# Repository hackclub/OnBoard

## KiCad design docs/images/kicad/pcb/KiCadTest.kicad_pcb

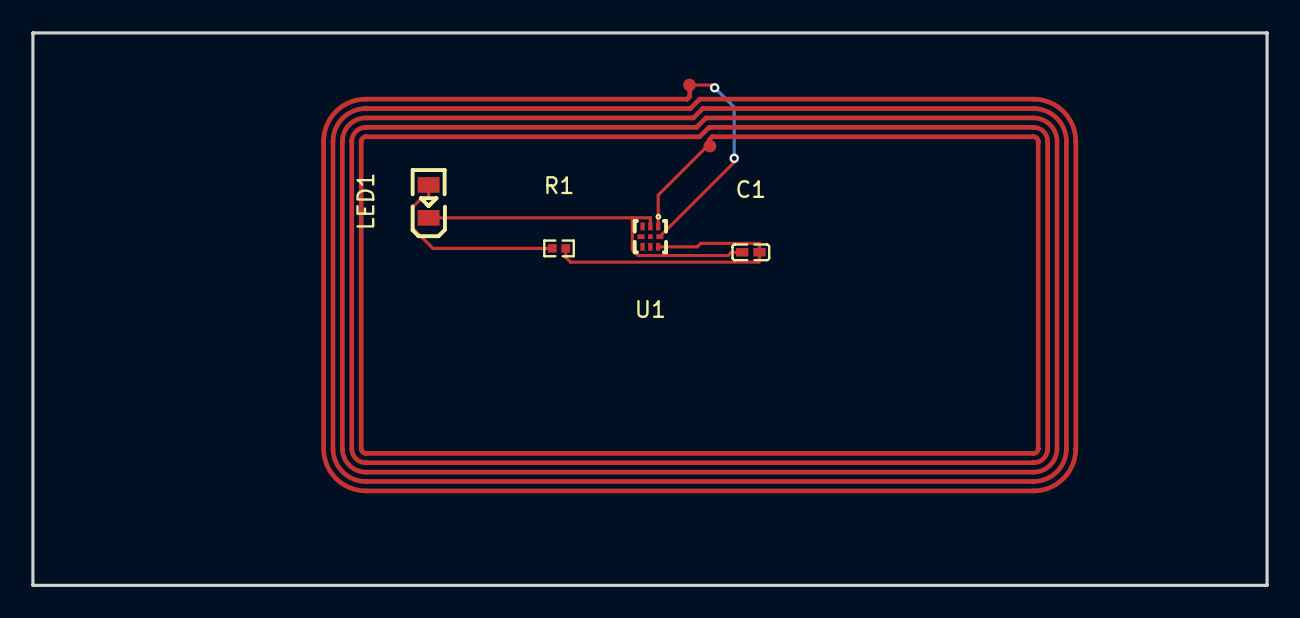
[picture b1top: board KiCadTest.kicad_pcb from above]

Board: 2 copper layers, 78.8 x 35.2 mm, 5 parts (0 on the bottom side), 3 nets.

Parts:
AE1: Antenna_Loop; 25X48MM_NFC_ANTENNA
C1: 220nF; C0402
LED1: 17-21SUYC/TR8; LED0805-R-RD
R1: 47; R0402
U1: NT3H2111W0FHKH; XQFN-8_L1.6-W1.6-P0.50-BL

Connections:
unnamed: LED1.1 (+), R1.1
unnamed: C1.1, LED1.2 (-), U1.2 (VSS)
unnamed: C1.2, R1.2, U1.7 (VOUT)

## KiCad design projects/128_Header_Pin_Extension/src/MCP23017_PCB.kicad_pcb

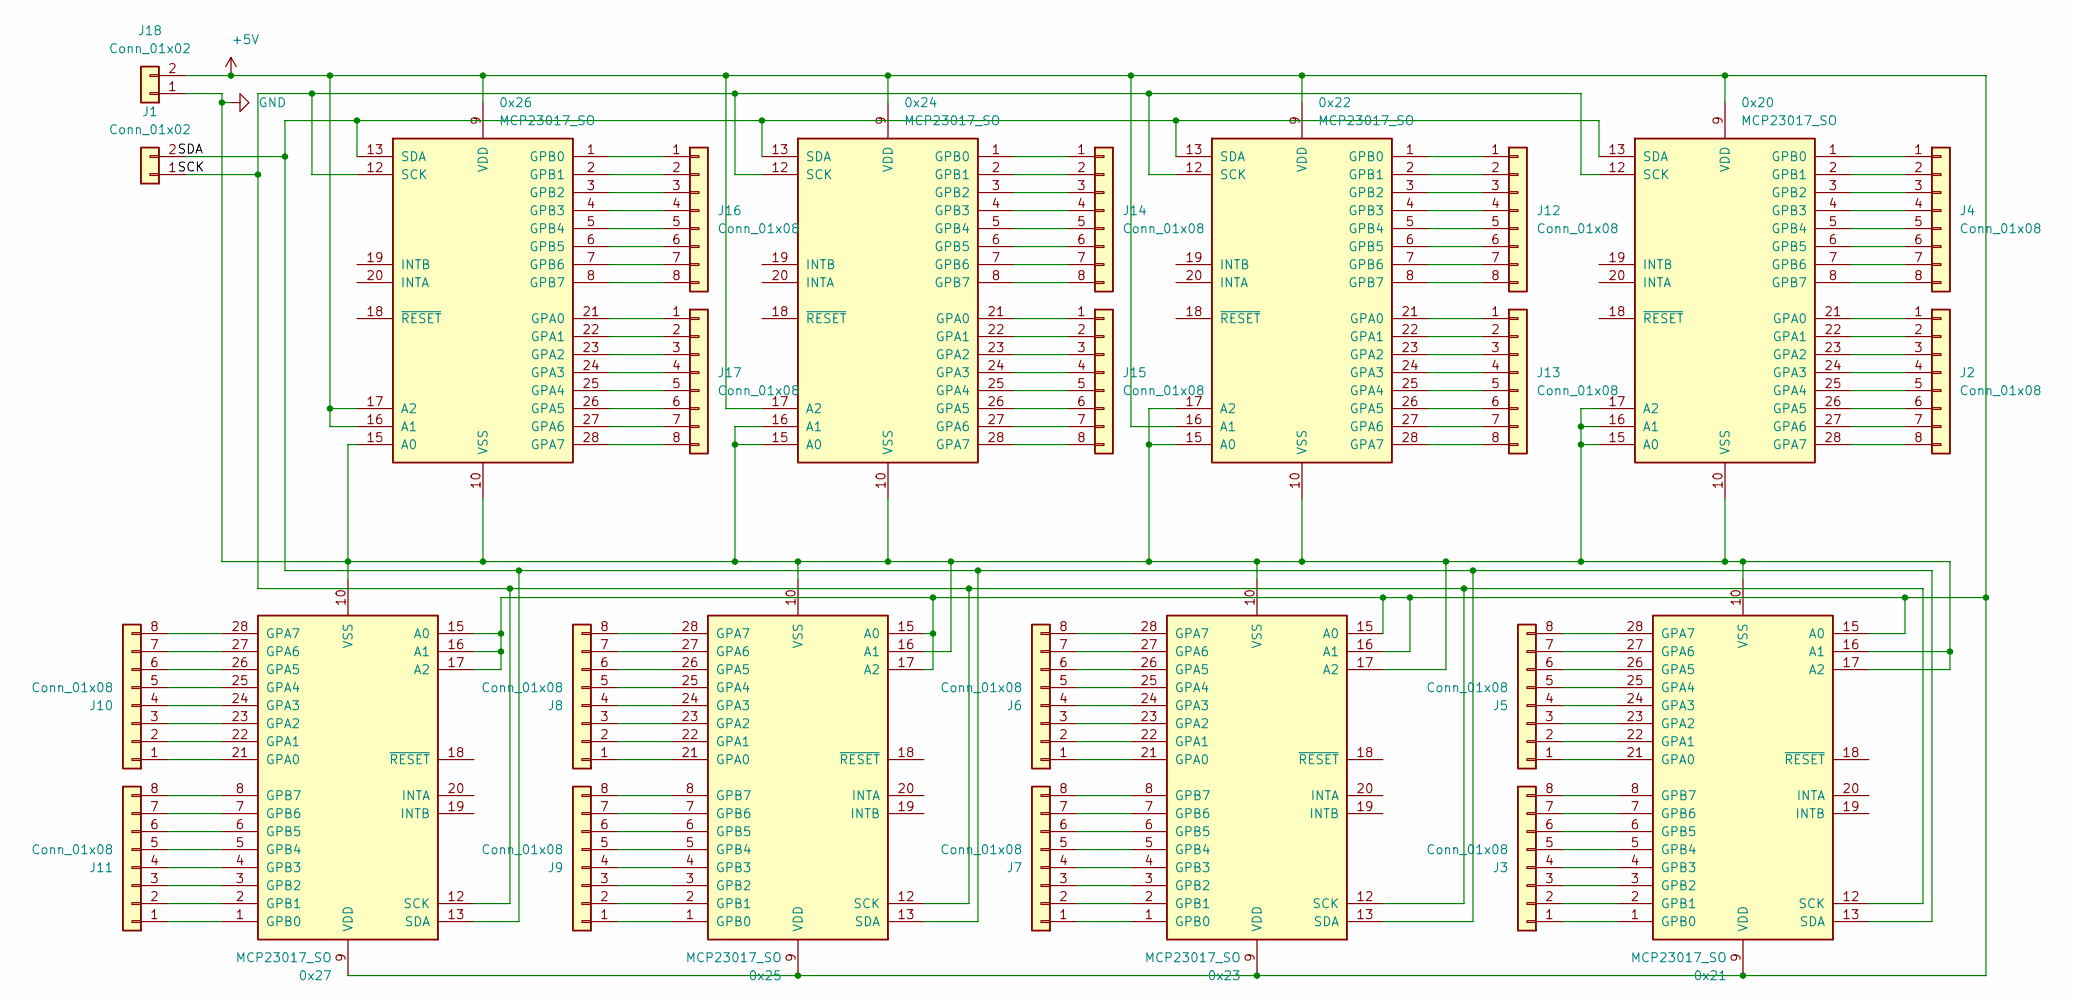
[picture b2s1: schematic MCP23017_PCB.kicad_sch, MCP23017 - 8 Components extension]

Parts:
0x20, 0x21, 0x22, 0x23, 0x24, 0x25, 0x26, 0x27: MCP23017_SO; SOIC-28W_7.5x17.9mm_P1.27mm
J1, J18: Conn_01x02; PinHeader_1x02_P2.00mm_Vertical
J2, J3, J4, J5, J6, J7, J8, J9, J10, J11, J12, J13, J14, J15, J16, J17: Conn_01x08; PinHeader_1x08_P2.00mm_Vertical

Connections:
+5V: 0x20.9 (VDD), 0x21.9 (VDD), 0x21.15 (A0), 0x22.9 (VDD), 0x22.16 (A1), 0x23.9 (VDD), 0x23.15 (A0), 0x23.16 (A1), 0x24.9 (VDD), 0x24.17 (A2), 0x25.9 (VDD), 0x25.15 (A0), 0x25.17 (A2), 0x26.9 (VDD), 0x26.16 (A1), 0x26.17 (A2), 0x27.9 (VDD), 0x27.15 (A0), 0x27.16 (A1), 0x27.17 (A2), J18.2
GND: 0x20.10 (VSS), 0x20.15 (A0), 0x20.16 (A1), 0x20.17 (A2), 0x21.10 (VSS), 0x21.16 (A1), 0x21.17 (A2), 0x22.10 (VSS), 0x22.15 (A0), 0x22.17 (A2), 0x23.10 (VSS), 0x23.17 (A2), 0x24.10 (VSS), 0x24.15 (A0), 0x24.16 (A1), 0x25.10 (VSS), 0x25.16 (A1), 0x26.10 (VSS), 0x26.15 (A0), 0x27.10 (VSS), J18.1
unnamed: 0x20.21 (GPA0), J2.1
unnamed: 0x20.22 (GPA1), J2.2
unnamed: 0x20.23 (GPA2), J2.3
unnamed: 0x20.24 (GPA3), J2.4
unnamed: 0x20.25 (GPA4), J2.5
unnamed: 0x20.26 (GPA5), J2.6
unnamed: 0x20.27 (GPA6), J2.7
unnamed: 0x20.28 (GPA7), J2.8
unnamed: 0x20.1 (GPB0), J4.1
unnamed: 0x20.2 (GPB1), J4.2
unnamed: 0x20.3 (GPB2), J4.3
unnamed: 0x20.4 (GPB3), J4.4
unnamed: 0x20.5 (GPB4), J4.5
unnamed: 0x20.6 (GPB5), J4.6
unnamed: 0x20.7 (GPB6), J4.7
unnamed: 0x20.8 (GPB7), J4.8
unnamed: 0x20.12 (SCK), 0x21.12 (SCK), 0x22.12 (SCK), 0x23.12 (SCK), 0x24.12 (SCK), 0x25.12 (SCK), 0x26.12 (SCK), 0x27.12 (SCK), J1.1
unnamed: 0x20.13 (SDA), 0x21.13 (SDA), 0x22.13 (SDA), 0x23.13 (SDA), 0x24.13 (SDA), 0x25.13 (SDA), 0x26.13 (SDA), 0x27.13 (SDA), J1.2
unnamed: 0x21.21 (GPA0), J5.1
unnamed: 0x21.22 (GPA1), J5.2
unnamed: 0x21.23 (GPA2), J5.3
unnamed: 0x21.24 (GPA3), J5.4
unnamed: 0x21.25 (GPA4), J5.5
unnamed: 0x21.26 (GPA5), J5.6
unnamed: 0x21.27 (GPA6), J5.7
unnamed: 0x21.28 (GPA7), J5.8
unnamed: 0x21.1 (GPB0), J3.1
unnamed: 0x21.2 (GPB1), J3.2
unnamed: 0x21.3 (GPB2), J3.3
unnamed: 0x21.4 (GPB3), J3.4
unnamed: 0x21.5 (GPB4), J3.5
unnamed: 0x21.6 (GPB5), J3.6
unnamed: 0x21.7 (GPB6), J3.7
unnamed: 0x21.8 (GPB7), J3.8
unnamed: 0x22.21 (GPA0), J13.1
unnamed: 0x22.22 (GPA1), J13.2
unnamed: 0x22.23 (GPA2), J13.3
unnamed: 0x22.24 (GPA3), J13.4
unnamed: 0x22.25 (GPA4), J13.5
unnamed: 0x22.26 (GPA5), J13.6
unnamed: 0x22.27 (GPA6), J13.7
unnamed: 0x22.28 (GPA7), J13.8
unnamed: 0x22.1 (GPB0), J12.1
unnamed: 0x22.2 (GPB1), J12.2
unnamed: 0x22.3 (GPB2), J12.3
unnamed: 0x22.4 (GPB3), J12.4
unnamed: 0x22.5 (GPB4), J12.5
unnamed: 0x22.6 (GPB5), J12.6
unnamed: 0x22.7 (GPB6), J12.7
unnamed: 0x22.8 (GPB7), J12.8
unnamed: 0x23.21 (GPA0), J6.1
unnamed: 0x23.22 (GPA1), J6.2
unnamed: 0x23.23 (GPA2), J6.3
unnamed: 0x23.24 (GPA3), J6.4
unnamed: 0x23.25 (GPA4), J6.5
unnamed: 0x23.26 (GPA5), J6.6
unnamed: 0x23.27 (GPA6), J6.7
unnamed: 0x23.28 (GPA7), J6.8
unnamed: 0x23.1 (GPB0), J7.1
unnamed: 0x23.2 (GPB1), J7.2
unnamed: 0x23.3 (GPB2), J7.3
unnamed: 0x23.4 (GPB3), J7.4
unnamed: 0x23.5 (GPB4), J7.5
unnamed: 0x23.6 (GPB5), J7.6
unnamed: 0x23.7 (GPB6), J7.7
unnamed: 0x23.8 (GPB7), J7.8
unnamed: 0x24.21 (GPA0), J15.1
unnamed: 0x24.22 (GPA1), J15.2
unnamed: 0x24.23 (GPA2), J15.3
unnamed: 0x24.24 (GPA3), J15.4
unnamed: 0x24.25 (GPA4), J15.5
unnamed: 0x24.26 (GPA5), J15.6
unnamed: 0x24.27 (GPA6), J15.7
unnamed: 0x24.28 (GPA7), J15.8
unnamed: 0x24.1 (GPB0), J14.1
unnamed: 0x24.2 (GPB1), J14.2
unnamed: 0x24.3 (GPB2), J14.3
unnamed: 0x24.4 (GPB3), J14.4
unnamed: 0x24.5 (GPB4), J14.5
unnamed: 0x24.6 (GPB5), J14.6
unnamed: 0x24.7 (GPB6), J14.7
unnamed: 0x24.8 (GPB7), J14.8
unnamed: 0x25.21 (GPA0), J8.1
unnamed: 0x25.22 (GPA1), J8.2
unnamed: 0x25.23 (GPA2), J8.3
unnamed: 0x25.24 (GPA3), J8.4
unnamed: 0x25.25 (GPA4), J8.5
unnamed: 0x25.26 (GPA5), J8.6
unnamed: 0x25.27 (GPA6), J8.7
unnamed: 0x25.28 (GPA7), J8.8
unnamed: 0x25.1 (GPB0), J9.1
unnamed: 0x25.2 (GPB1), J9.2
unnamed: 0x25.3 (GPB2), J9.3
unnamed: 0x25.4 (GPB3), J9.4
unnamed: 0x25.5 (GPB4), J9.5
unnamed: 0x25.6 (GPB5), J9.6
unnamed: 0x25.7 (GPB6), J9.7
unnamed: 0x25.8 (GPB7), J9.8
unnamed: 0x26.21 (GPA0), J17.1
unnamed: 0x26.22 (GPA1), J17.2
unnamed: 0x26.23 (GPA2), J17.3
unnamed: 0x26.24 (GPA3), J17.4
unnamed: 0x26.25 (GPA4), J17.5
unnamed: 0x26.26 (GPA5), J17.6
unnamed: 0x26.27 (GPA6), J17.7
unnamed: 0x26.28 (GPA7), J17.8
unnamed: 0x26.1 (GPB0), J16.1
unnamed: 0x26.2 (GPB1), J16.2
unnamed: 0x26.3 (GPB2), J16.3
unnamed: 0x26.4 (GPB3), J16.4
unnamed: 0x26.5 (GPB4), J16.5
unnamed: 0x26.6 (GPB5), J16.6
unnamed: 0x26.7 (GPB6), J16.7
unnamed: 0x26.8 (GPB7), J16.8
unnamed: 0x27.21 (GPA0), J10.1
unnamed: 0x27.22 (GPA1), J10.2
unnamed: 0x27.23 (GPA2), J10.3
unnamed: 0x27.24 (GPA3), J10.4
unnamed: 0x27.25 (GPA4), J10.5
unnamed: 0x27.26 (GPA5), J10.6
unnamed: 0x27.27 (GPA6), J10.7
unnamed: 0x27.28 (GPA7), J10.8
unnamed: 0x27.1 (GPB0), J11.1
unnamed: 0x27.2 (GPB1), J11.2
unnamed: 0x27.3 (GPB2), J11.3
unnamed: 0x27.4 (GPB3), J11.4
unnamed: 0x27.5 (GPB4), J11.5
unnamed: 0x27.6 (GPB5), J11.6
unnamed: 0x27.7 (GPB6), J11.7
unnamed: 0x27.8 (GPB7), J11.8

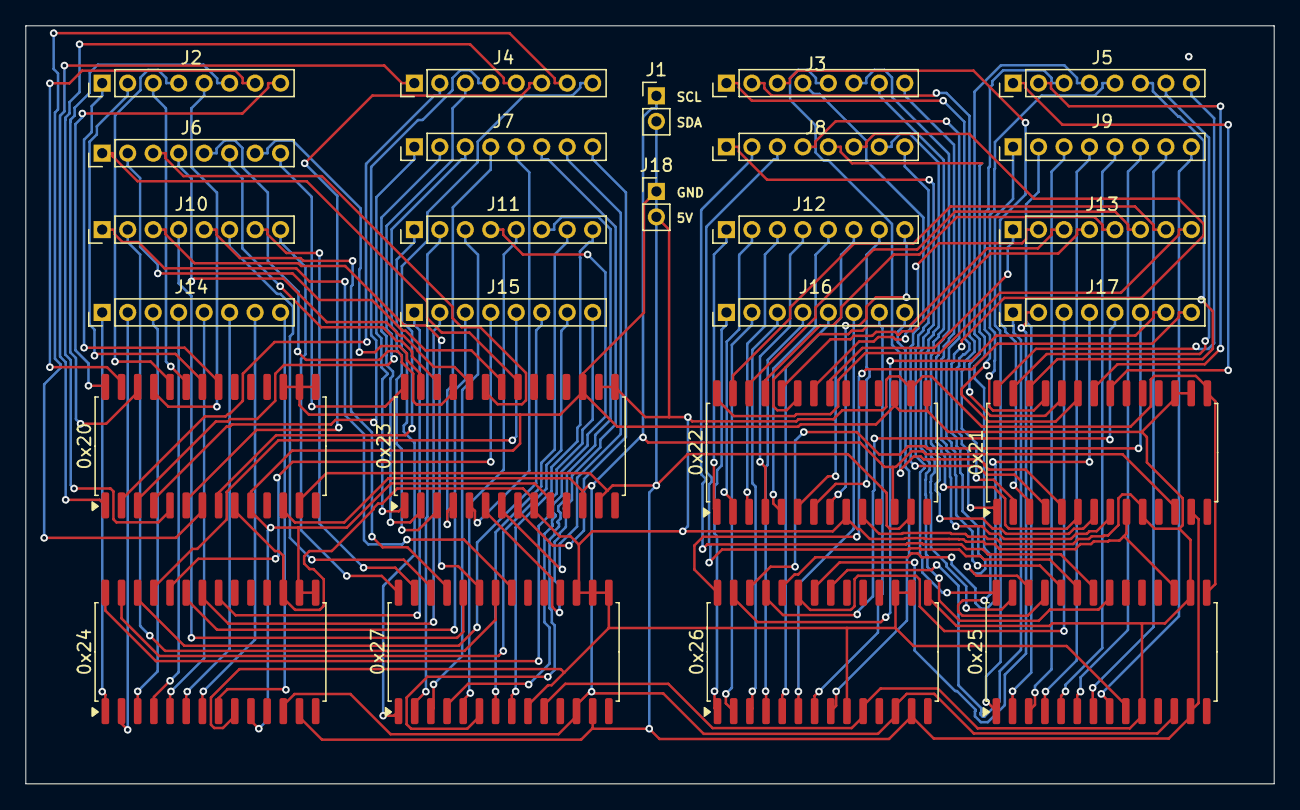
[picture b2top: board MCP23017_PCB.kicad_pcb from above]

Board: 2 copper layers, 98.0 x 59.5 mm, 26 parts (0 on the bottom side), 132 nets.

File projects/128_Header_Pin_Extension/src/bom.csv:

Designator,Footprint,Quantity,Value,LCSC Part #
"0X20, 0X21, 0X22, 0X23, 0X24, 0X25, 0X26, 0X27",SOIC-28W_7.5x17.9mm_P1.27mm,8,MCP23017_SO,MCP23017-E/SO
"J1, J18",PinHeader_1x02_P2.00mm_Vertical,2,Conn_01x02,MTP220-1102S1
"J10, J11, J12, J13, J14, J15, J16, J17, J2, J3, J4, J5, J6, J7, J8, J9",PinHeader_1x08_P2.00mm_Vertical,16,Conn_01x08,A2005WV-8P

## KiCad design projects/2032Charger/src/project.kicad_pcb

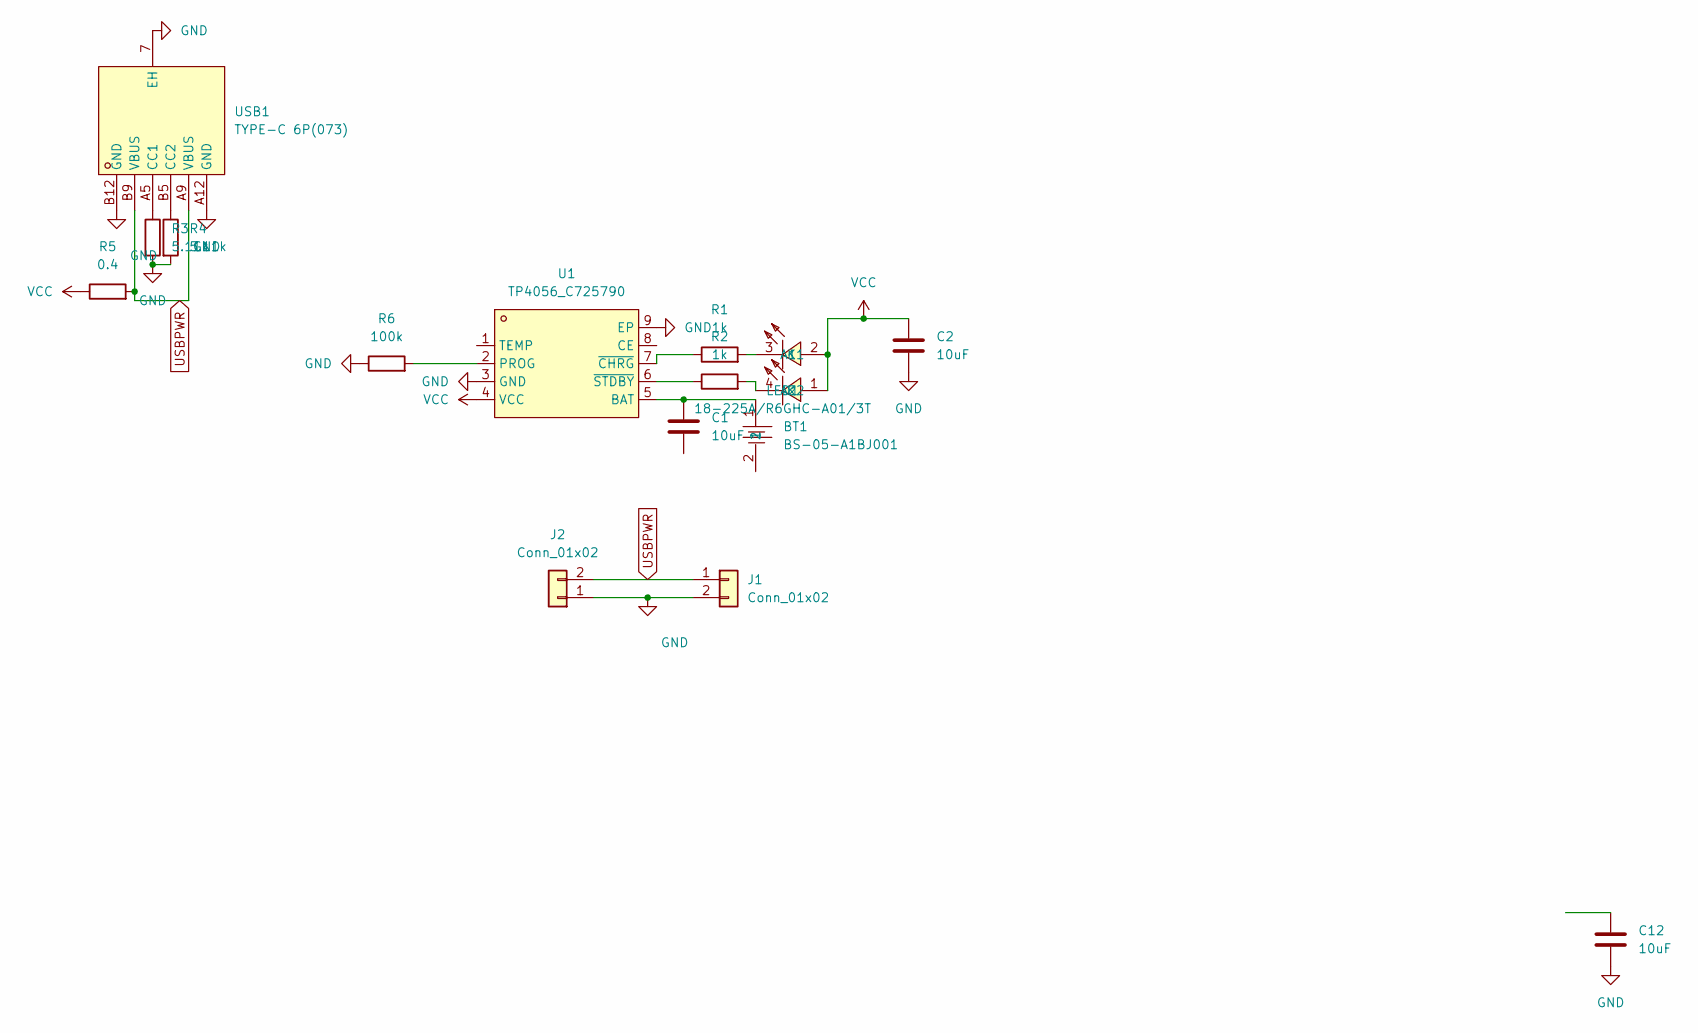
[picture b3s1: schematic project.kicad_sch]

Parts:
BT1: BS-05-A1BJ001; BAT-TH_BS-05-A1BJ001; LCSC Part C964752
C1, C2, C12: 10uF; C_0603_1608Metric; LCSC C1691
J1: Conn_01x02; PinSocket_1x02_P2.54mm_Horizontal
J2: Conn_01x02; PinHeader_1x02_P2.54mm_Horizontal
LED1: 18-225A/R6GHC-A01/3T; LED-SMD_4P-L1.6-W0.8-BR-RD; LCSC Part C264440
R1, R2: 1k; R_0603_1608Metric; LCSC C21190
R3, R4: 5.11k; R_0603_1608Metric; LCSC C112314
R5: 0.4; R_0603_1608Metric; LCSC C5126047
R6: 100k; R_0603_1608Metric; LCSC C14675
U1: TP4056_C725790; ESOP-8_L4.9-W3.9-P1.27-LS6.0-BL-EP; LCSC Part C725790
USB1: TYPE-C 6P(073); TYPE-C-SMD_TYPE-C-6P_5; LCSC Part C668623

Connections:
GND: BT1.2, C1.2, C2.2, C12.2, J1.2, J2.1, R3.2, R4.2, R6.1, U1.3 (GND), U1.9 (EP), USB1.7 (EH), USB1.A12 (GND), USB1.B12 (GND)
unnamed: LED1.3 (K1), R1.2
unnamed: LED1.4 (K2), R2.2
unnamed: BT1.1, C1.1, U1.5 (BAT)
unnamed: R6.2, U1.2 (PROG)
unnamed: R1.1, U1.7 (~CHRG)
unnamed: R2.1, U1.6 (~STDBY)
unnamed: R3.1, USB1.A5 (CC1)
unnamed: R4.1, USB1.B5 (CC2)
USBPWR: J1.1, J2.2, R5.2, USB1.A9 (VBUS), USB1.B9 (VBUS)
VCC: C2.1, LED1.1 (A2), LED1.2 (A1), R5.1, U1.4 (VCC)

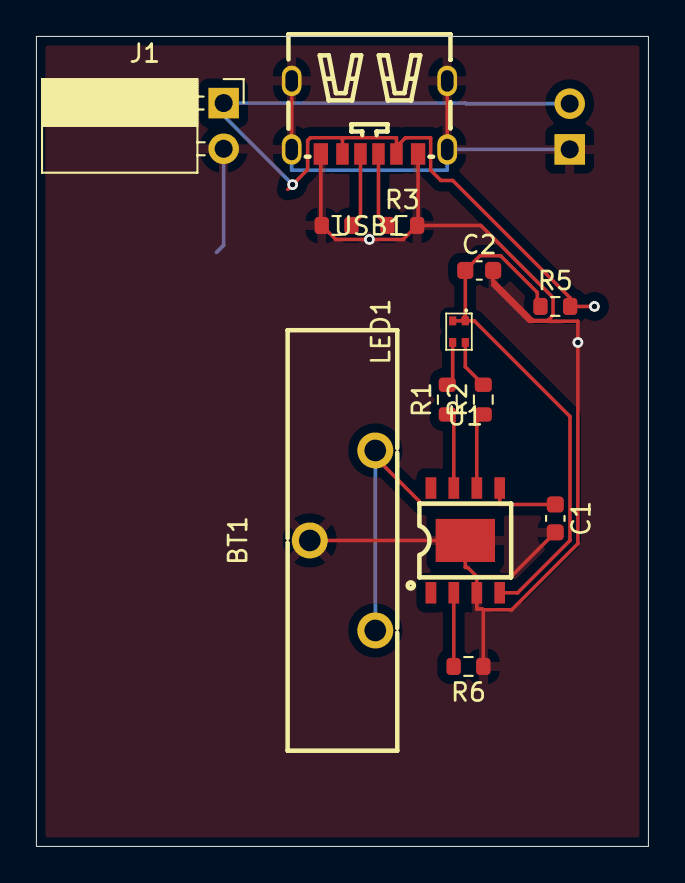
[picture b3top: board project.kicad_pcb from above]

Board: 2 copper layers, 34.0 x 45.0 mm, 14 parts (1 on the bottom side), 11 nets.

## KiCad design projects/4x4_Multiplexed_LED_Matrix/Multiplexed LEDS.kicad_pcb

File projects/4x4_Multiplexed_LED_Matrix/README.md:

---
name: "Adrian Rangel"
slack_handle: "@Rangel"
github_handle: "@AdrianRang"
tutorial: NA
---

# 4x4 Multiplexed LED Matrix

I always wanted to learn how to drive an LED Matrix so I went for it and designed the PCB, its a 4 by 4 grid driven by 8 io pins on an arduino NANO.

Price for 5 boards:
- Manufacturing $2.00
- Shipping $17.80
- Components $428.40MXN / 25.71 US dollars
- TOTAL: $55.51
> [!NOTE]
> Components will be bought locally hence the price in MXN

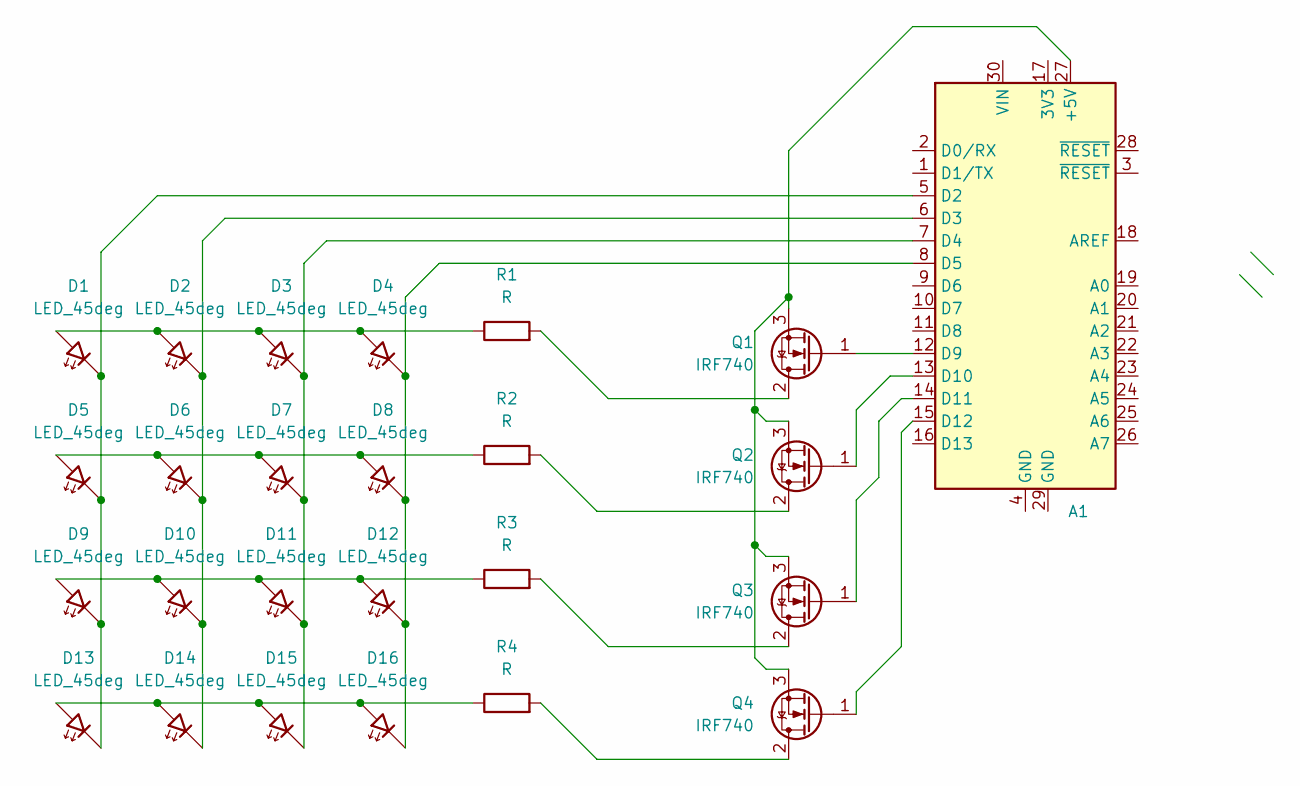
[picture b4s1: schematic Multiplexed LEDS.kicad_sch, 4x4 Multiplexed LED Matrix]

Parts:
A1: Arduino_Nano_v2.x; Arduino_Nano
D1, D2, D3, D4, D5, D6, D7, D8, D9, D10, D11, D12, D13, D14, D15, D16: LED_45deg; LED_D5.0mm
Q1, Q2, Q3, Q4: IRF740; TO-220-3_Vertical
R1, R2, R3, R4: R; R_Axial_DIN0309_L9.0mm_D3.2mm_P15.24mm_Horizontal

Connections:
unnamed: A1.27 (+5V), Q1.3 (S), Q2.3 (S), Q3.3 (S), Q4.3 (S)
unnamed: A1.5 (D2), D1.1 (K), D5.1 (K), D9.1 (K), D13.1 (K)
unnamed: A1.6 (D3), D2.1 (K), D6.1 (K), D10.1 (K), D14.1 (K)
unnamed: A1.7 (D4), D3.1 (K), D7.1 (K), D11.1 (K), D15.1 (K)
unnamed: A1.8 (D5), D4.1 (K), D8.1 (K), D12.1 (K), D16.1 (K)
unnamed: A1.12 (D9), Q1.1 (G)
unnamed: A1.13 (D10), Q2.1 (G)
unnamed: A1.14 (D11), Q3.1 (G)
unnamed: A1.15 (D12), Q4.1 (G)
unnamed: D1.2 (A), D2.2 (A), D3.2 (A), D4.2 (A), R1.1
unnamed: D5.2 (A), D6.2 (A), D7.2 (A), D8.2 (A), R2.1
unnamed: D9.2 (A), D10.2 (A), D11.2 (A), D12.2 (A), R3.1
unnamed: D13.2 (A), D14.2 (A), D15.2 (A), D16.2 (A), R4.1
unnamed: Q1.2 (D), R1.2
unnamed: Q2.2 (D), R2.2
unnamed: Q3.2 (D), R3.2
unnamed: Q4.2 (D), R4.2

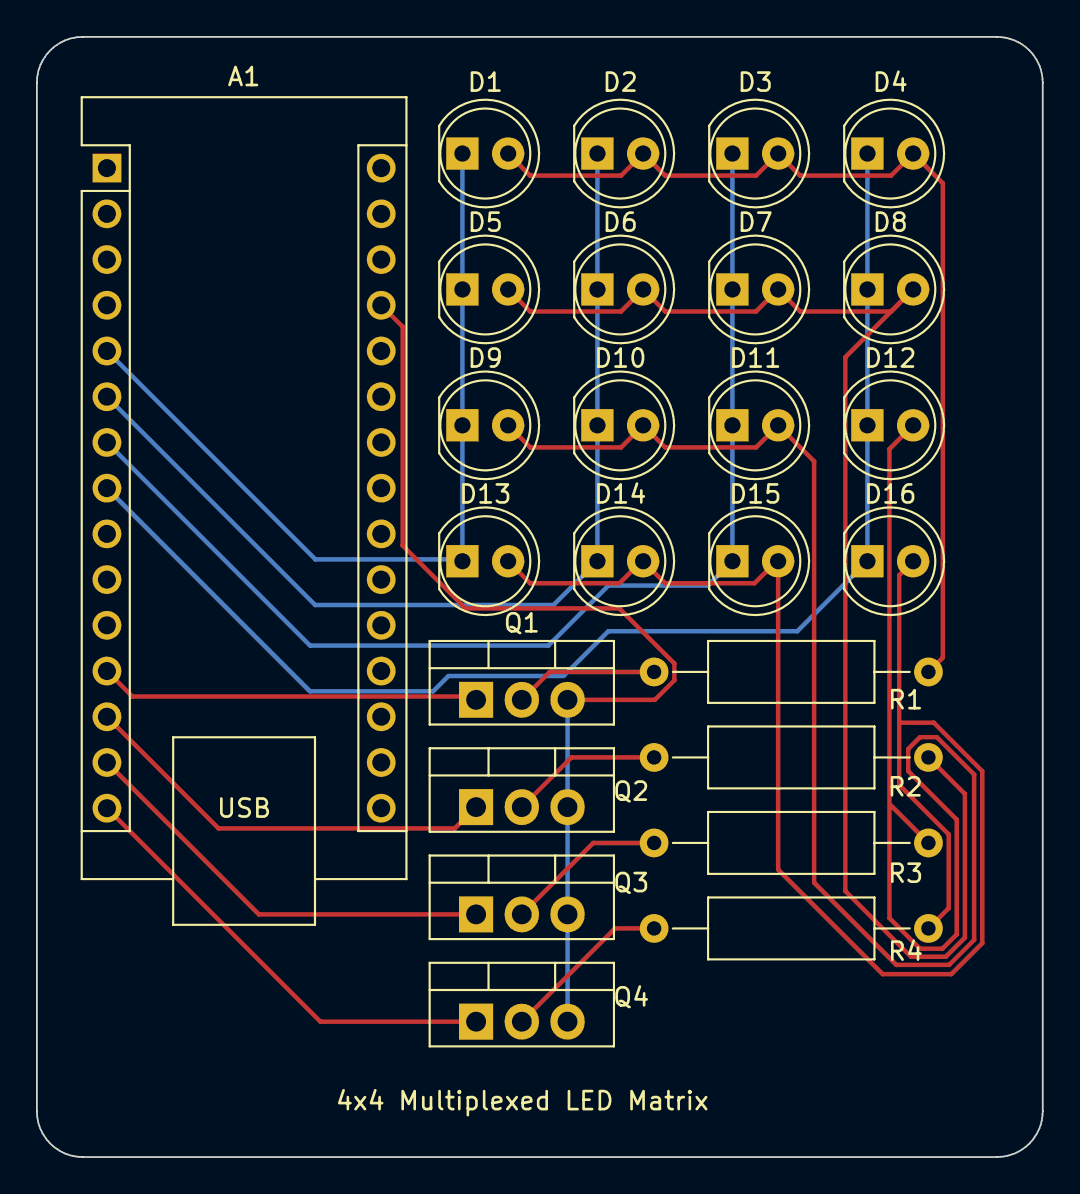
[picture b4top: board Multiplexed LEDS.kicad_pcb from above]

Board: 2 copper layers, 55.9 x 62.2 mm, 25 parts (0 on the bottom side), 17 nets.

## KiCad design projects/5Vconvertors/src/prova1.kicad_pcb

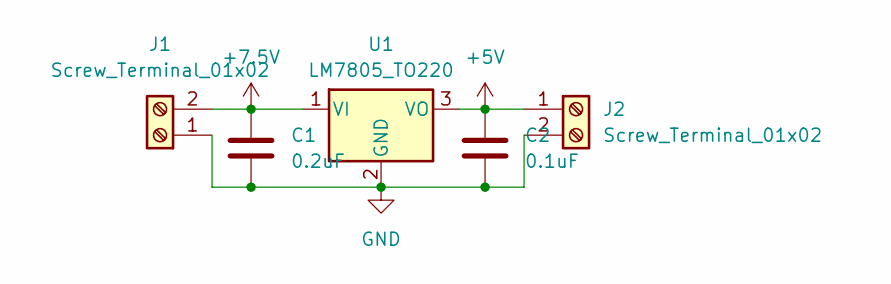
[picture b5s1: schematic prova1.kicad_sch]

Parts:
C1: 0.2uF; C_1206_3216Metric
C2: 0.1uF; C_1206_3216Metric
J1, J2: Screw_Terminal_01x02; TerminalBlock_Phoenix_MKDS-1,5-2-5.08_1x02_P5.08mm_Horizont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
U1: LM7805_TO220; TO-220-3_Vertical

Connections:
+5V: C2.1, J2.1, U1.3 (VO)
+7.5V: C1.1, J1.2, U1.1 (VI)
GND: C1.2, C2.2, J1.1, J2.2, U1.2 (GND)

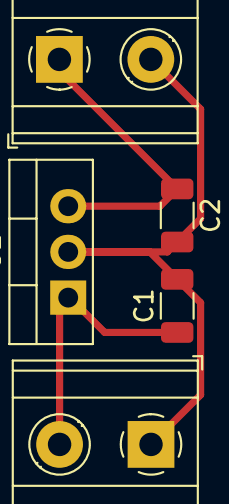
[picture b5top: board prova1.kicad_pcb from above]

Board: 2 copper layers, 5 parts (0 on the bottom side), 3 nets.

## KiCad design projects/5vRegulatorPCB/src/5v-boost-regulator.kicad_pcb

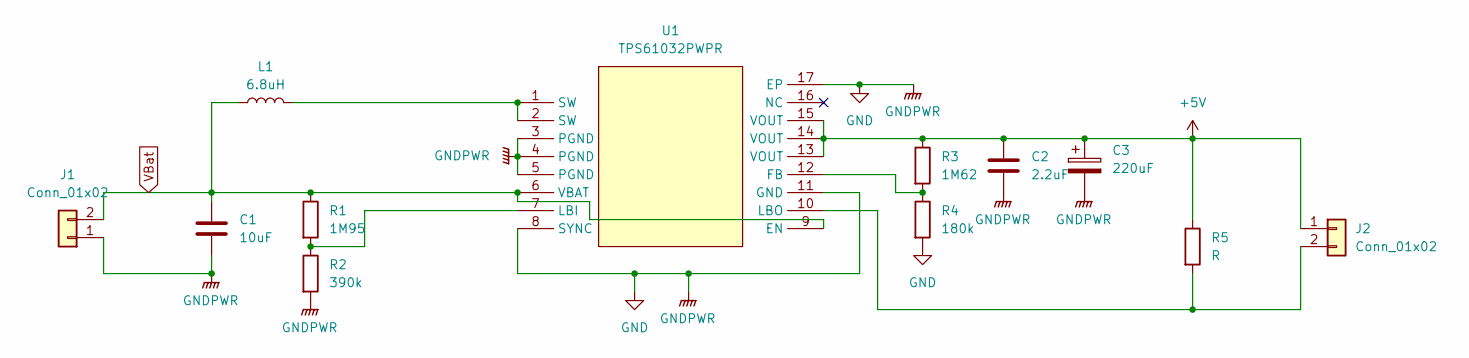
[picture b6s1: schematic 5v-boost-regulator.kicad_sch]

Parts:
C1: 10uF; C_1206_3216Metric
C2: 2.2uF; C_1206_3216Metric
C3: 220uF; CP_Elec_6.3x7.7; LCSC C2887273
J1, J2: Conn_01x02; PinHeader_1x02_P2.54mm_Horizontal
L1: 6.8uH; L_Sunlord_MWSA1004S; LCSC C2921230
R1: 1M95; R_1206_3216Metric
R2: 390k; R_1206_3216Metric
R3: 1M62; R_1206_3216Metric
R4: 180k; R_1206_3216Metric
R5: R; R_1206_3216Metric
U1: TPS61032PWPR; HTSSOP-16_L5.0-W4.4-P0.65-LS6.4-BL-EP; LCSC Part C88716

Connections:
+5V: C2.1, C3.1, J2.1, R3.1, R5.1, U1.13 (VOUT), U1.14 (VOUT), U1.15 (VOUT)
GND: C1.2, C2.2, C3.2, J1.1, R2.2, R4.2, U1.3 (PGND), U1.4 (PGND), U1.5 (PGND), U1.8 (SYNC), U1.11 (GND), U1.17 (EP)
unnamed: J2.2, R5.2, U1.10 (LBO)
unnamed: L1.1, U1.1 (SW), U1.2 (SW)
unnamed: R3.2, R4.1, U1.12 (FB)
unnamed: R1.2, R2.1, U1.7 (LBI)
VBat: C1.1, J1.2, L1.2, R1.1, U1.6 (VBAT), U1.9 (EN)

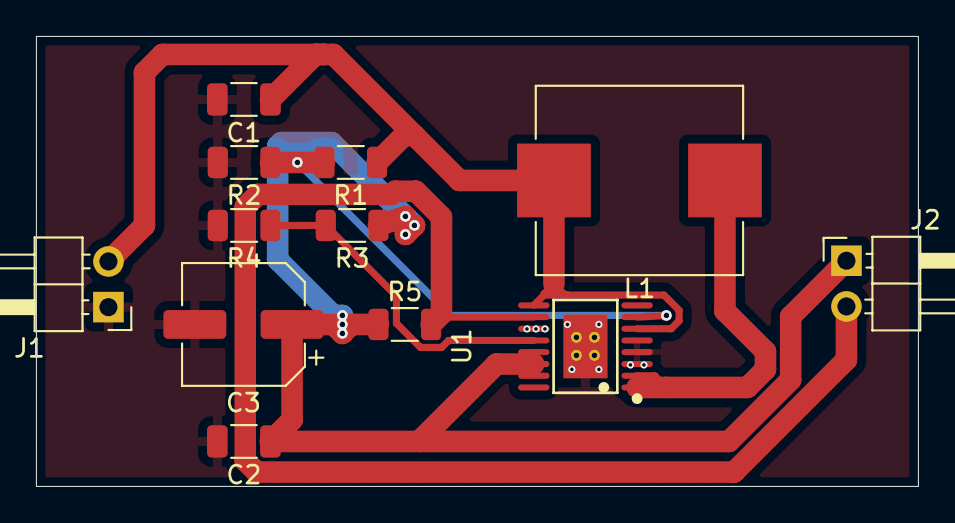
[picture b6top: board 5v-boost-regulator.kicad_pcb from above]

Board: 2 copper layers, 49.0 x 25.0 mm, 12 parts (0 on the bottom side), 7 nets.
